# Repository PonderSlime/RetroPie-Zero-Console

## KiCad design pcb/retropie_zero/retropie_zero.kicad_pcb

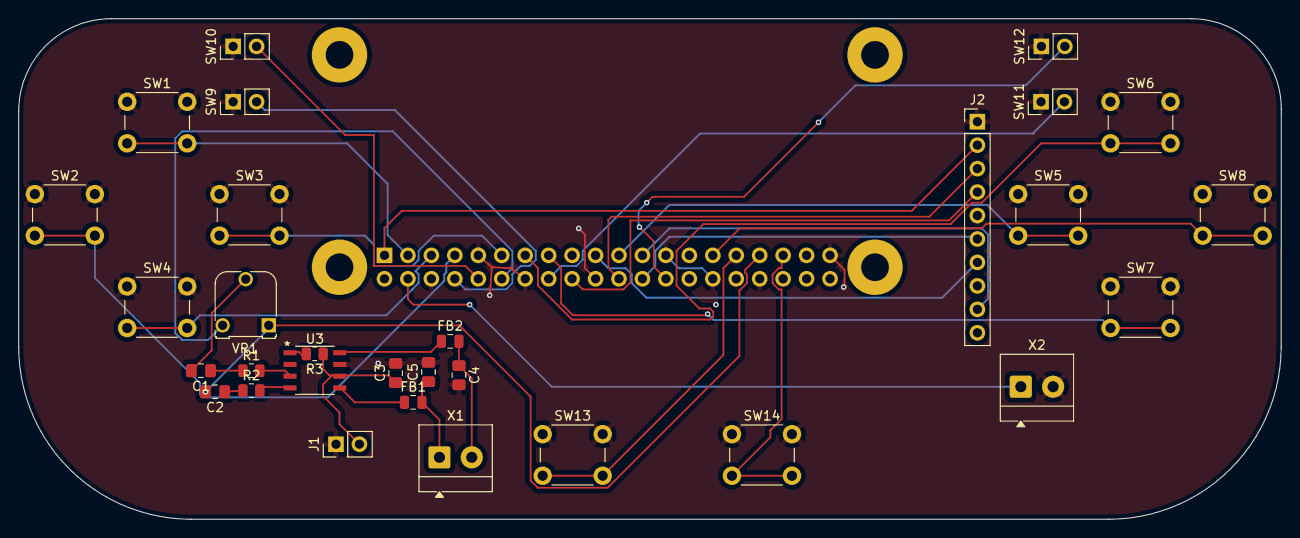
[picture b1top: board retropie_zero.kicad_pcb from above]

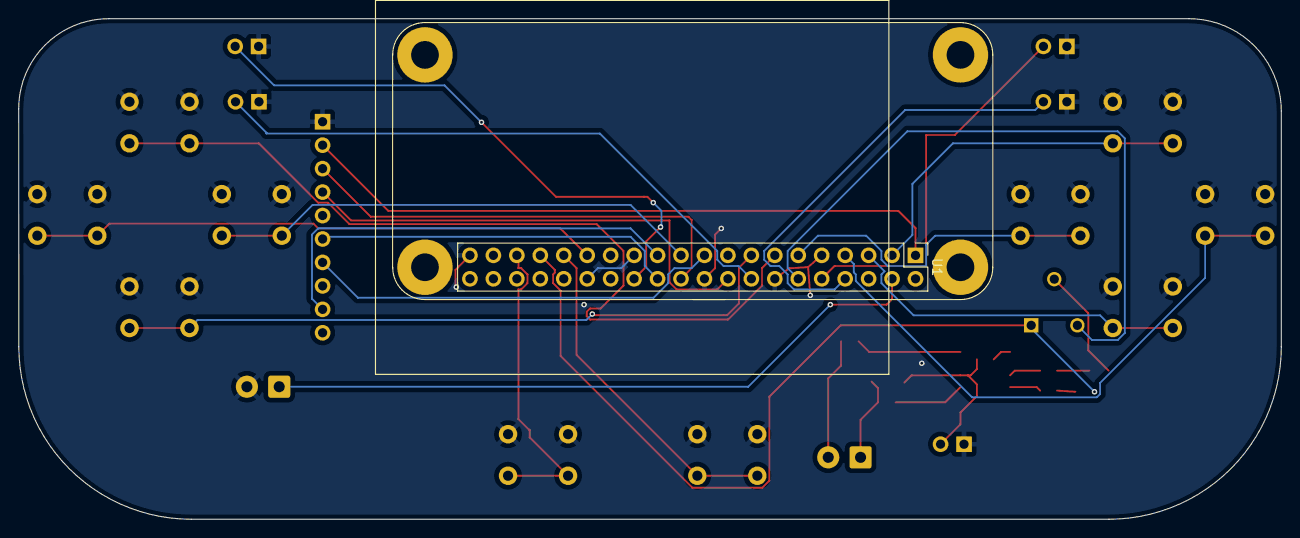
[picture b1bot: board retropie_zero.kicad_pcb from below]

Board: 2 copper layers, 136.8 x 54.2 mm, 32 parts (2 on the bottom side), 35 nets.

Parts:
C1, C2: 1uF; C_0805_2012Metric_Pad1.18x1.45mm_HandSolder
C3: 10uF; C_0805_2012Metric_Pad1.18x1.45mm_HandSolder
C4, C5: 220pF; C_0805_2012Metric_Pad1.18x1.45mm_HandSolder
FB1, FB2: Ferrite; C_0805_2012Metric
J1: Conn_01x02_Socket; PinHeader_1x02_P2.54mm_Vertical
J2: Conn_01x10_Pin; PinHeader_1x10_P2.54mm_Vertical
R1, R2: 100; R_0805_2012Metric
R3: 10K; R_0805_2012Metric
SW1, SW2, SW3, SW4, SW5, SW6, SW7, SW8, SW13, SW14: SW_DIP_x01; SW_PUSH_6mm
SW9, SW10, SW11, SW12: SW_DIP_x01; PinHeader_1x02_P2.54mm_Vertical
U1: TM022HDH26_2.2IN_LCD
U1#2: RPI Zero Footprint
U3: PAM8302AASCR; PAM8302AADCR
VR1: 10K trim; Potentiometer_Runtron_RM-065_Vertical
X1, X2: TERMBLOCK_1X2; TerminalBlock_4Ucon_1x02_P3.50mm_Horizontal

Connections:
+3V3: J2.2, U1#2.1 (3V3)
/SD: R3.2, U3.1 (/SD)
/VO+: C5.1, FB1.2, X1.1
/VO-: C4.1, FB2.2, X1.2
AIN +: U1#2.12 (GPIO18), VR1.3 (E)
AIN -: C2.2, U1#2.33 (GPIO13), VR1.1 (A)
DPAD_D: SW4.2, U1#2.5 (GPIO3)
DPAD_L: SW2.2, U1#2.7 (GPIO4)
DPAD_R: SW3.2, U1#2.11 (GPIO17)
DPAD_U: SW1.2, U1#2.3 (GPIO2)
GND: C3.2, C4.2, C5.2, J1.1, J2.1, SW1.1, SW2.1, SW3.1, SW4.1, SW5.1, SW6.1, SW7.1, SW8.1, SW9.1, SW10.1, SW11.1, SW12.1, SW13.1, SW14.1, U1#2.6 (GND), U1#2.9 (GND), U1#2.14 (GND), U1#2.20 (GND), U1#2.25 (GND), U1#2.30 (GND), U1#2.34 (GND), U1#2.39 (GND), U3.7 (GND), X2.2
L_BUMP: SW9.2, U1#2.8 (GPIO14)
L_TRIG: SW10.2, U1#2.10 (GPIO15)
unnamed: C1.1, R1.1
unnamed: C2.1, R2.1
unnamed: FB1.1, U3.5 (VO_P)
unnamed: FB2.1, U3.8 (VO_N)
unnamed: R2.2, U3.4 (IN_N)
unnamed: R1.2, U3.3 (IN_P)
unnamed: C1.2, VR1.2 (S)
PowerBoost Power: U1#2.4 (VBUS), X2.1
R_BUMP: SW11.2, U1#2.16 (GPIO23)
R_TRIG: SW12.2, U1#2.26 (GPIO7)
SCREEN_CLK: J2.9, U1#2.23 (GPIO11)
SCREEN_CS: J2.6, U1#2.24 (GPIO8)
SCREEN_D_C: J2.3, U1#2.22 (GPIO25)
SCREEN_MOSI: J2.7, U1#2.19 (GPIO10)
SCREEN_RST: J2.4, U1#2.18 (GPIO24)
SW_A: SW8.2, U1#2.29 (GPIO5)
SW_B: SW7.2, U1#2.15 (GPIO22)
SW_SEL: SW13.2, U1#2.31 (GPIO6)
SW_STA: SW14.2, U1#2.35 (GPIO19)
SW_X: SW6.2, U1#2.13 (GPIO27)
SW_Y: SW5.2, U1#2.21 (GPIO9)
VCC: C3.1, J1.2, R3.1, U3.6 (VDD)

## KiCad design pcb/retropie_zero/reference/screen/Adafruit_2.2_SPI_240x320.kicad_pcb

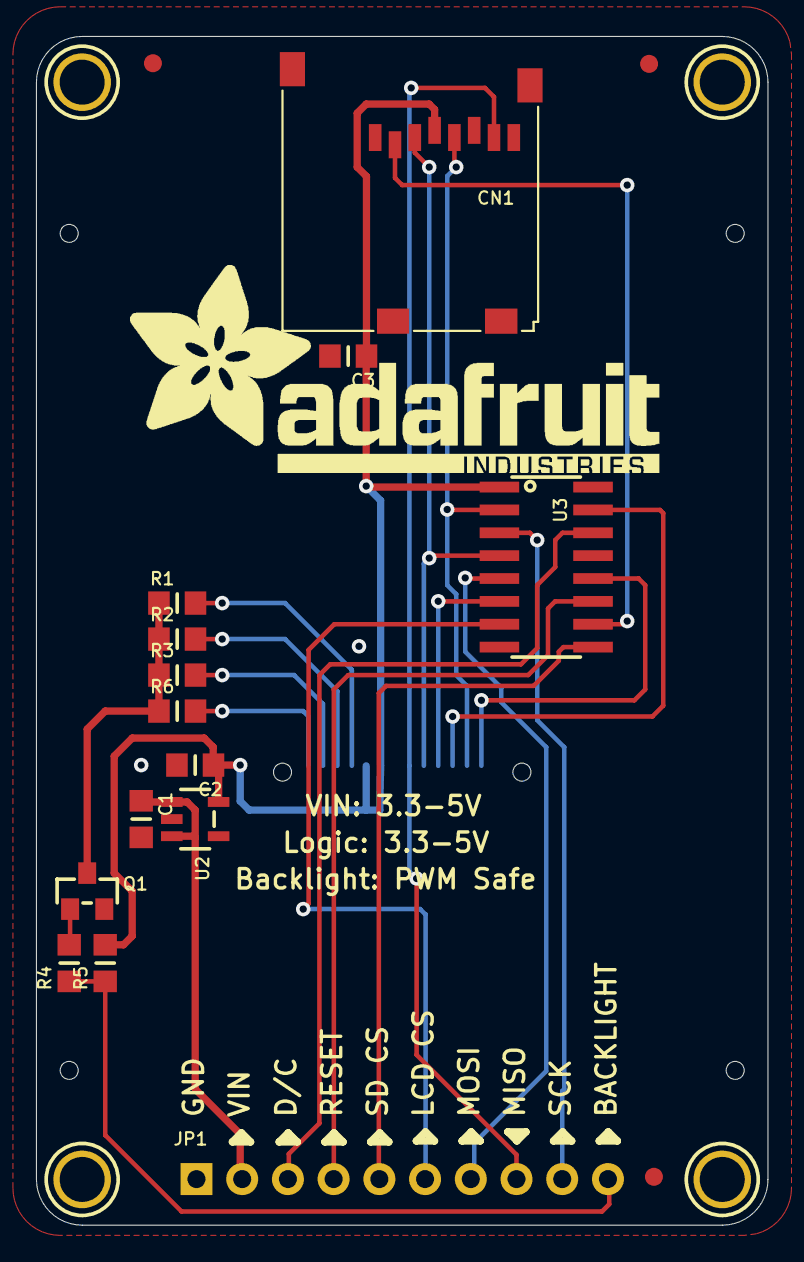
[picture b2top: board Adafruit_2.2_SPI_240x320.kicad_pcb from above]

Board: 2 copper layers, 40.6 x 66.0 mm, 23 parts (1 on the bottom side), 23 nets.

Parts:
C1, C2, C3: 10uF; _0805MP
CN1: MICROSD
FID1, FID2, FID3: FIDUCIAL""; FIDUCIAL_1MM
JP1: 1X10_ROUND70
Q1: 2N2222; SOT23-WIDE
R1, R2, R3, R6: 10; _0805MP
R4: 1K; _0805MP
R5: 10K; _0805MP
U1: TM022HDH26_2.2IN_LCD
U2: RT9193-3.3; SOT23-5
U3: 74HC4050D; SOIC16
U$2, U$3, U$4, U$5: MOUNTINGHOLE2.5; MOUNTINGHOLE_2.5_PLATED
U$20: ADAFRUIT_TEXT_30MM

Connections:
3.3V: C2.1, C3.1, CN1.4, R5.2, U1.9, U1.10, U2.5, U3.1
BACKLIGHT: JP1.10, R4.1, R5.1
DC_3V: U1.4, U3.15
DC_5V: JP1.3, U3.14
GND: C1.2, C2.2, C3.2, CN1.6, CN1.MT1, CN1.MT2, JP1.1, Q1.2, U1.1, U1.8, U2.2, U3.8
LCDCS_3V: U1.5, U3.6
LCDCS_5V: JP1.6, U3.7
LEDK: Q1.3, R1.1, R2.1, R3.1, R6.1
MISO: CN1.7, JP1.8, U1.7
MOSI_3V: CN1.3, U1.6, U3.4
MOSI_5V: JP1.7, U3.5
unnamed: R1.2, U1.11
unnamed: R2.2, U1.12
unnamed: R3.2, U1.13
unnamed: Q1.1, R4.2
unnamed: R6.2, U1.14
RESET_3V: U1.2, U3.12
RESET_5V: JP1.4, U3.11
SCLK_3V: CN1.5, U1.3, U3.2
SCLK_5V: JP1.9, U3.3
SDCS_3V: CN1.2, U3.10
SDCS_5V: JP1.5, U3.9
VIN: C1.1, JP1.2, U2.1, U2.3

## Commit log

2025-04-17 Added lib files
2025-04-17 Added Reference for sound, finished schematic
2025-04-18 Fixed some stuff, removed irrelevant reference
2025-04-18 Assigned footprints, ignoring backups now
2025-04-18 PCB Routing finished
2025-04-18 Wiring finished
2025-04-18 Board Outline Fixed
2025-04-18 Fixed resistor placement
2025-04-18 Clarified RPI Zero Header Placement

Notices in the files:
parts and their libraries:
Copyright 2021 Accelerated Designs. All rights reserved.
